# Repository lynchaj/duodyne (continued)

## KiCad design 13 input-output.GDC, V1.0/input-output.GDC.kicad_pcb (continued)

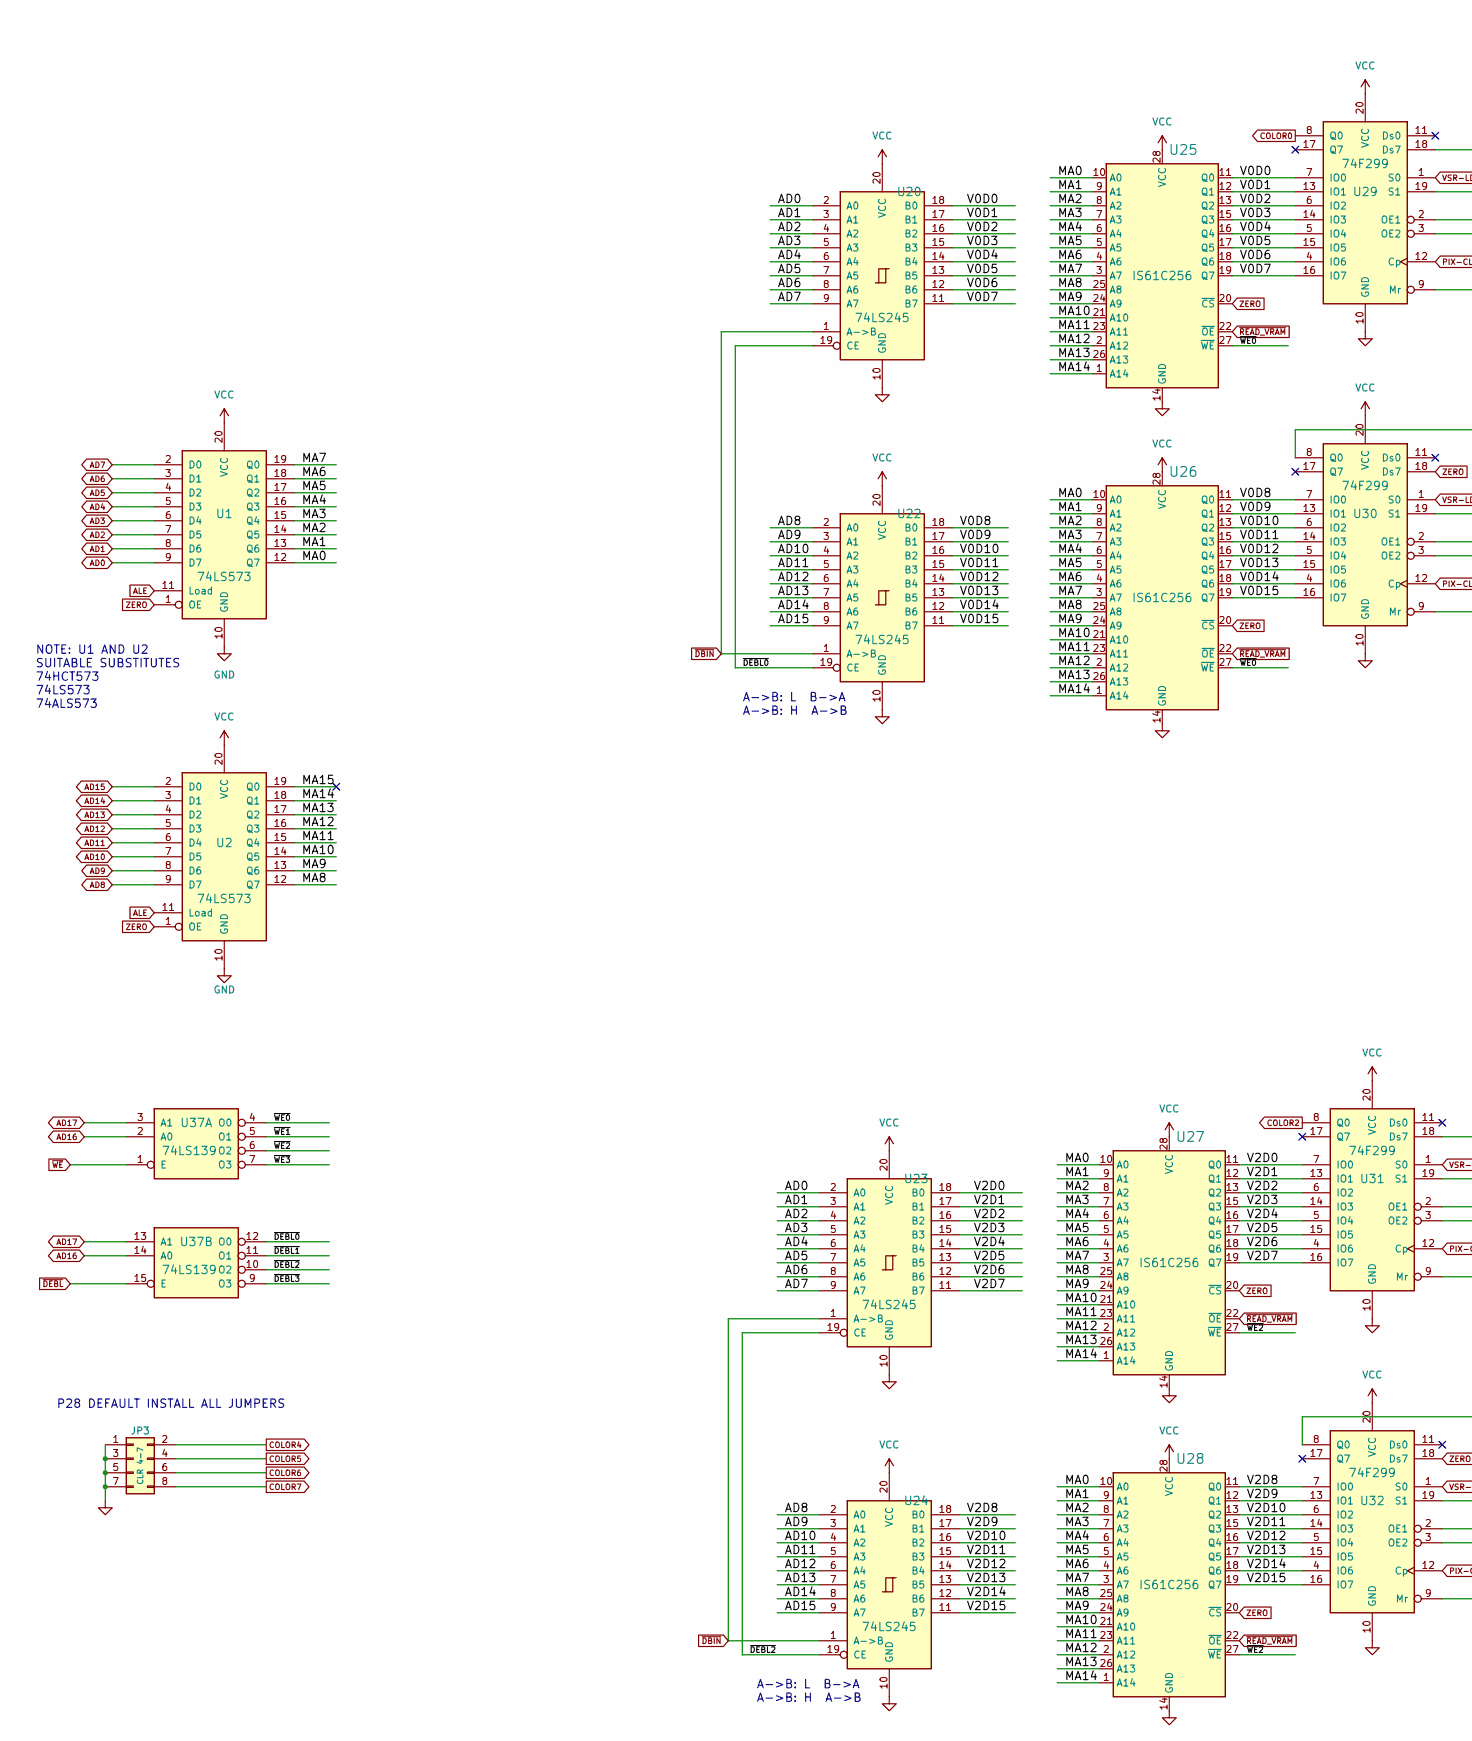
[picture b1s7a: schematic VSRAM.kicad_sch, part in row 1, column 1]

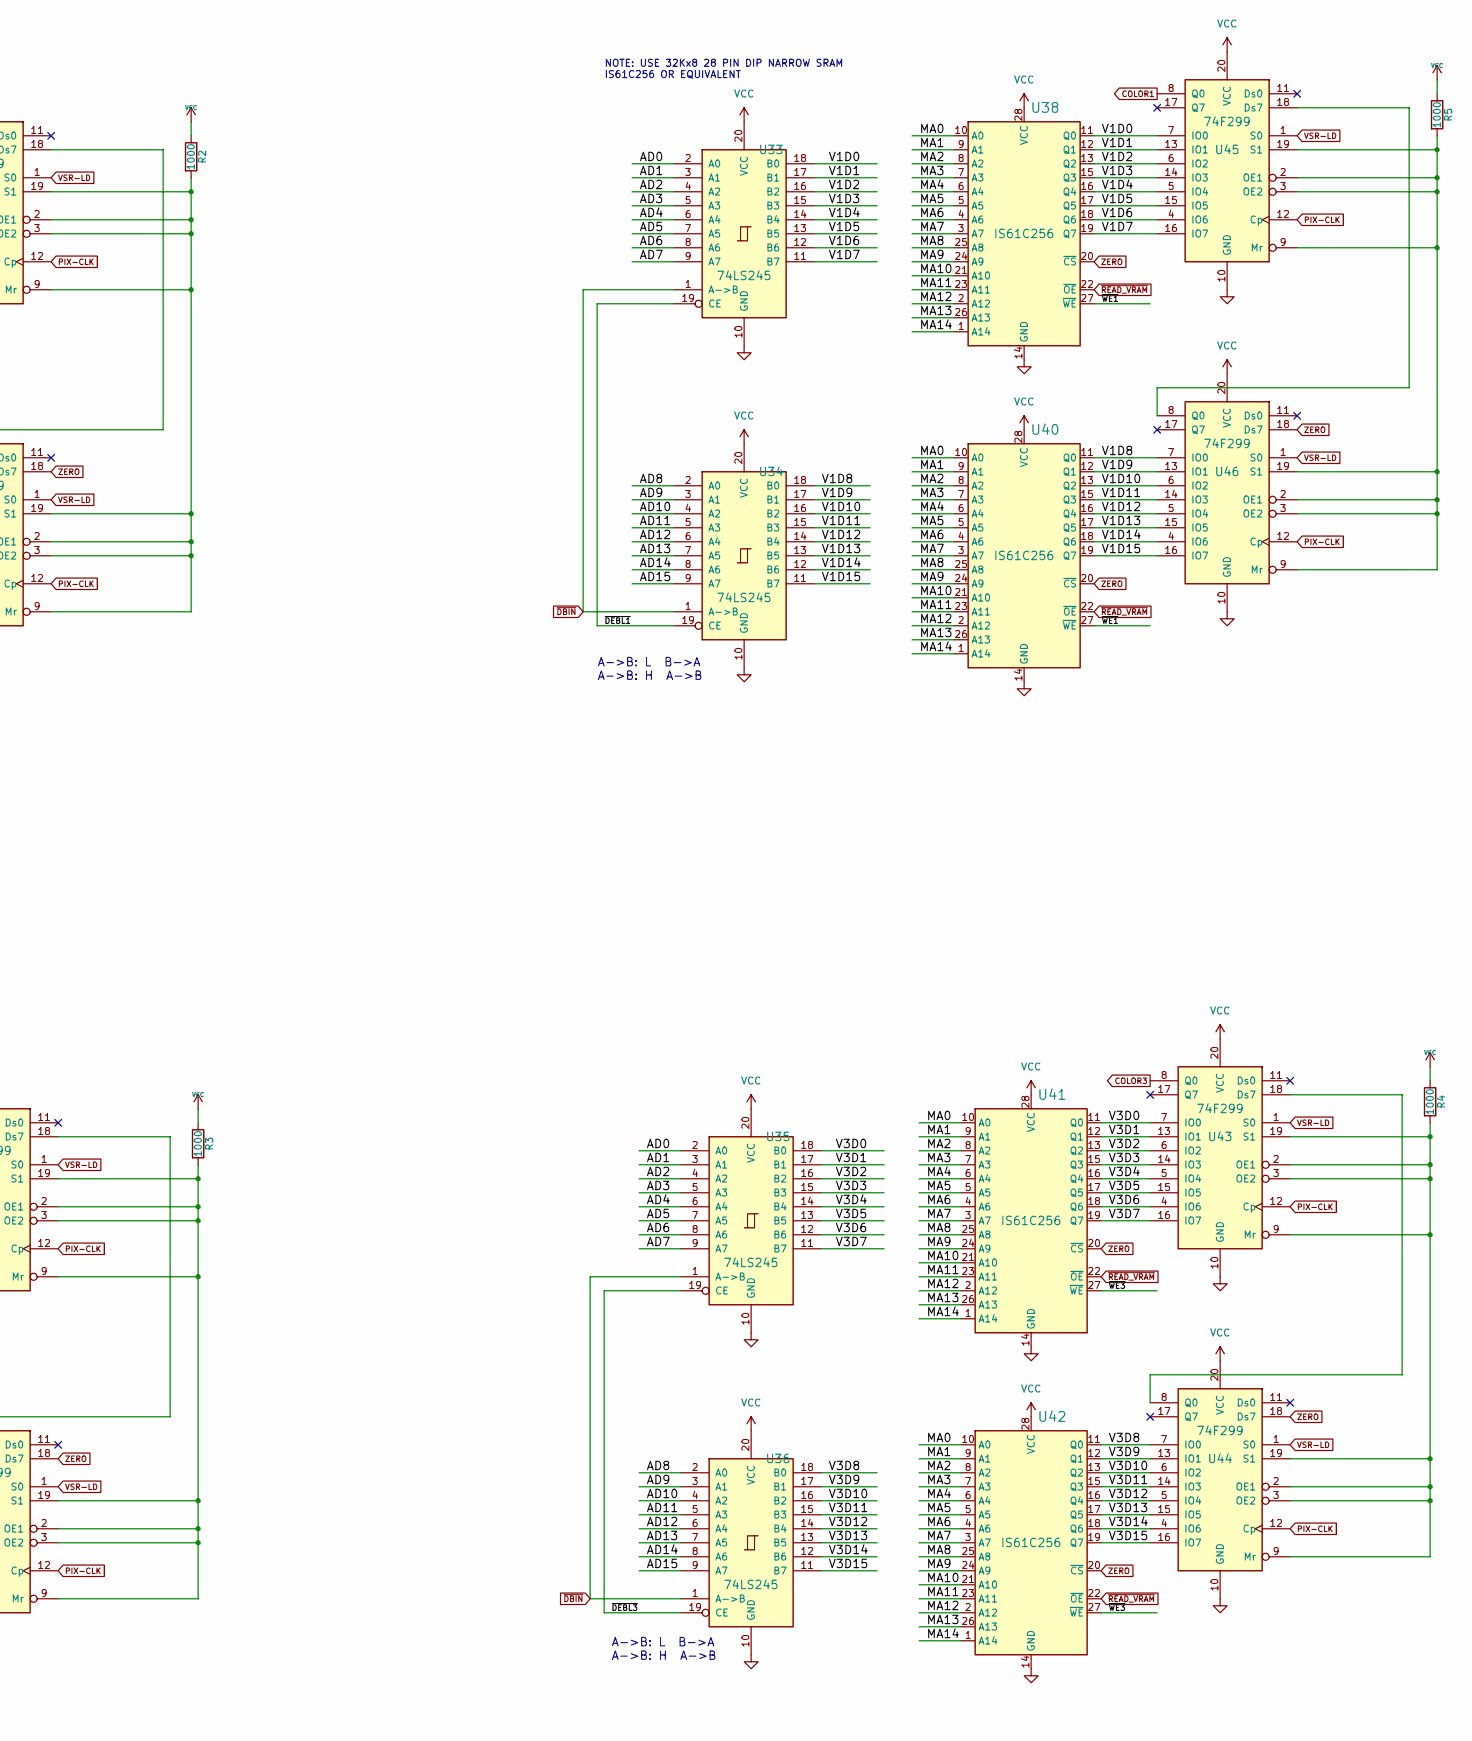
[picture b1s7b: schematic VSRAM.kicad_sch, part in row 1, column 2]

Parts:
JP3: CLR 4-7; PinHeader_2x04_P2.54mm_Vertical
R2, R3, R4, R5: 1000; R_Axial_DIN0207_L6.3mm_D2.5mm_P7.62mm_Horizontal
U1, U2: 74LS573; DIP-20_W7.62mm_Socket
U20, U22, U23, U24, U33, U34, U35, U36: 74LS245; DIP-20_W7.62mm_Socket
U25, U26, U27, U28, U38, U40, U41, U42: IS61C256; DIP-28_W7.62mm_Socket
U29, U30, U31, U32, U43, U44, U45, U46: 74F299; DIP-20_W7.62mm_Socket
U37: 74LS139; DIP-16_W7.62mm_Socket

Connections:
/VSRAM/MA0: U1.12 (Q7), U25.10 (A0), U26.10 (A0), U27.10 (A0), U28.10 (A0), U38.10 (A0), U40.10 (A0), U41.10 (A0), U42.10 (A0)
/VSRAM/MA1: U1.13 (Q6), U25.9 (A1), U26.9 (A1), U27.9 (A1), U28.9 (A1), U38.9 (A1), U40.9 (A1), U41.9 (A1), U42.9 (A1)
/VSRAM/MA2: U1.14 (Q5), U25.8 (A2), U26.8 (A2), U27.8 (A2), U28.8 (A2), U38.8 (A2), U40.8 (A2), U41.8 (A2), U42.8 (A2)
/VSRAM/MA3: U1.15 (Q4), U25.7 (A3), U26.7 (A3), U27.7 (A3), U28.7 (A3), U38.7 (A3), U40.7 (A3), U41.7 (A3), U42.7 (A3)
/VSRAM/MA4: U1.16 (Q3), U25.6 (A4), U26.6 (A4), U27.6 (A4), U28.6 (A4), U38.6 (A4), U40.6 (A4), U41.6 (A4), U42.6 (A4)
/VSRAM/MA5: U1.17 (Q2), U25.5 (A5), U26.5 (A5), U27.5 (A5), U28.5 (A5), U38.5 (A5), U40.5 (A5), U41.5 (A5), U42.5 (A5)
/VSRAM/MA6: U1.18 (Q1), U25.4 (A6), U26.4 (A6), U27.4 (A6), U28.4 (A6), U38.4 (A6), U40.4 (A6), U41.4 (A6), U42.4 (A6)
/VSRAM/MA7: U1.19 (Q0), U25.3 (A7), U26.3 (A7), U27.3 (A7), U28.3 (A7), U38.3 (A7), U40.3 (A7), U41.3 (A7), U42.3 (A7)
/VSRAM/MA8: U2.12 (Q7), U25.25 (A8), U26.25 (A8), U27.25 (A8), U28.25 (A8), U38.25 (A8), U40.25 (A8), U41.25 (A8), U42.25 (A8)
/VSRAM/MA9: U2.13 (Q6), U25.24 (A9), U26.24 (A9), U27.24 (A9), U28.24 (A9), U38.24 (A9), U40.24 (A9), U41.24 (A9), U42.24 (A9)
/VSRAM/MA10: U2.14 (Q5), U25.21 (A10), U26.21 (A10), U27.21 (A10), U28.21 (A10), U38.21 (A10), U40.21 (A10), U41.21 (A10), U42.21 (A10)
/VSRAM/MA11: U2.15 (Q4), U25.23 (A11), U26.23 (A11), U27.23 (A11), U28.23 (A11), U38.23 (A11), U40.23 (A11), U41.23 (A11), U42.23 (A11)
/VSRAM/MA12: U2.16 (Q3), U25.2 (A12), U26.2 (A12), U27.2 (A12), U28.2 (A12), U38.2 (A12), U40.2 (A12), U41.2 (A12), U42.2 (A12)
/VSRAM/MA13: U2.17 (Q2), U25.26 (A13), U26.26 (A13), U27.26 (A13), U28.26 (A13), U38.26 (A13), U40.26 (A13), U41.26 (A13), U42.26 (A13)
/VSRAM/MA14: U2.18 (Q1), U25.1 (A14), U26.1 (A14), U27.1 (A14), U28.1 (A14), U38.1 (A14), U40.1 (A14), U41.1 (A14), U42.1 (A14)
/VSRAM/MA15: U2.19 (Q0)
/VSRAM/V0D0: U20.18 (B0), U25.11 (Q0), U29.7 (IO0)
/VSRAM/V0D1: U20.17 (B1), U25.12 (Q1), U29.13 (IO1)
/VSRAM/V0D2: U20.16 (B2), U25.13 (Q2), U29.6 (IO2)
/VSRAM/V0D3: U20.15 (B3), U25.15 (Q3), U29.14 (IO3)
/VSRAM/V0D4: U20.14 (B4), U25.16 (Q4), U29.5 (IO4)
/VSRAM/V0D5: U20.13 (B5), U25.17 (Q5), U29.15 (IO5)
/VSRAM/V0D6: U20.12 (B6), U25.18 (Q6), U29.4 (IO6)
/VSRAM/V0D7: U20.11 (B7), U25.19 (Q7), U29.16 (IO7)
/VSRAM/V0D8: U22.18 (B0), U26.11 (Q0), U30.7 (IO0)
/VSRAM/V0D9: U22.17 (B1), U26.12 (Q1), U30.13 (IO1)
/VSRAM/V0D10: U22.16 (B2), U26.13 (Q2), U30.6 (IO2)
/VSRAM/V0D11: U22.15 (B3), U26.15 (Q3), U30.14 (IO3)
/VSRAM/V0D12: U22.14 (B4), U26.16 (Q4), U30.5 (IO4)
/VSRAM/V0D13: U22.13 (B5), U26.17 (Q5), U30.15 (IO5)
/VSRAM/V0D14: U22.12 (B6), U26.18 (Q6), U30.4 (IO6)
/VSRAM/V0D15: U22.11 (B7), U26.19 (Q7), U30.16 (IO7)
/VSRAM/V1D0: U33.18 (B0), U38.11 (Q0), U45.7 (IO0)
/VSRAM/V1D1: U33.17 (B1), U38.12 (Q1), U45.13 (IO1)
/VSRAM/V1D2: U33.16 (B2), U38.13 (Q2), U45.6 (IO2)
/VSRAM/V1D3: U33.15 (B3), U38.15 (Q3), U45.14 (IO3)
/VSRAM/V1D4: U33.14 (B4), U38.16 (Q4), U45.5 (IO4)
/VSRAM/V1D5: U33.13 (B5), U38.17 (Q5), U45.15 (IO5)
/VSRAM/V1D6: U33.12 (B6), U38.18 (Q6), U45.4 (IO6)
/VSRAM/V1D7: U33.11 (B7), U38.19 (Q7), U45.16 (IO7)
/VSRAM/V1D8: U34.18 (B0), U40.11 (Q0), U46.7 (IO0)
/VSRAM/V1D9: U34.17 (B1), U40.12 (Q1), U46.13 (IO1)
/VSRAM/V1D10: U34.16 (B2), U40.13 (Q2), U46.6 (IO2)
/VSRAM/V1D11: U34.15 (B3), U40.15 (Q3), U46.14 (IO3)
/VSRAM/V1D12: U34.14 (B4), U40.16 (Q4), U46.5 (IO4)
/VSRAM/V1D13: U34.13 (B5), U40.17 (Q5), U46.15 (IO5)
/VSRAM/V1D14: U34.12 (B6), U40.18 (Q6), U46.4 (IO6)
/VSRAM/V1D15: U34.11 (B7), U40.19 (Q7), U46.16 (IO7)
/VSRAM/V2D0: U23.18 (B0), U27.11 (Q0), U31.7 (IO0)
/VSRAM/V2D1: U23.17 (B1), U27.12 (Q1), U31.13 (IO1)
/VSRAM/V2D2: U23.16 (B2), U27.13 (Q2), U31.6 (IO2)
/VSRAM/V2D3: U23.15 (B3), U27.15 (Q3), U31.14 (IO3)
/VSRAM/V2D4: U23.14 (B4), U27.16 (Q4), U31.5 (IO4)
/VSRAM/V2D5: U23.13 (B5), U27.17 (Q5), U31.15 (IO5)
/VSRAM/V2D6: U23.12 (B6), U27.18 (Q6), U31.4 (IO6)
/VSRAM/V2D7: U23.11 (B7), U27.19 (Q7), U31.16 (IO7)
/VSRAM/V2D8: U24.18 (B0), U28.11 (Q0), U32.7 (IO0)
/VSRAM/V2D9: U24.17 (B1), U28.12 (Q1), U32.13 (IO1)
/VSRAM/V2D10: U24.16 (B2), U28.13 (Q2), U32.6 (IO2)
/VSRAM/V2D11: U24.15 (B3), U28.15 (Q3), U32.14 (IO3)
/VSRAM/V2D12: U24.14 (B4), U28.16 (Q4), U32.5 (IO4)
/VSRAM/V2D13: U24.13 (B5), U28.17 (Q5), U32.15 (IO5)
/VSRAM/V2D14: U24.12 (B6), U28.18 (Q6), U32.4 (IO6)
/VSRAM/V2D15: U24.11 (B7), U28.19 (Q7), U32.16 (IO7)
/VSRAM/V3D0: U35.18 (B0), U41.11 (Q0), U43.7 (IO0)
/VSRAM/V3D1: U35.17 (B1), U41.12 (Q1), U43.13 (IO1)
/VSRAM/V3D2: U35.16 (B2), U41.13 (Q2), U43.6 (IO2)
/VSRAM/V3D3: U35.15 (B3), U41.15 (Q3), U43.14 (IO3)
/VSRAM/V3D4: U35.14 (B4), U41.16 (Q4), U43.5 (IO4)
/VSRAM/V3D5: U35.13 (B5), U41.17 (Q5), U43.15 (IO5)
/VSRAM/V3D6: U35.12 (B6), U41.18 (Q6), U43.4 (IO6)
/VSRAM/V3D7: U35.11 (B7), U41.19 (Q7), U43.16 (IO7)
/VSRAM/V3D8: U36.18 (B0), U42.11 (Q0), U44.7 (IO0)
/VSRAM/V3D9: U36.17 (B1), U42.12 (Q1), U44.13 (IO1)
/VSRAM/V3D10: U36.16 (B2), U42.13 (Q2), U44.6 (IO2)
/VSRAM/V3D11: U36.15 (B3), U42.15 (Q3), U44.14 (IO3)
/VSRAM/V3D12: U36.14 (B4), U42.16 (Q4), U44.5 (IO4)
/VSRAM/V3D13: U36.13 (B5), U42.17 (Q5), U44.15 (IO5)
/VSRAM/V3D14: U36.12 (B6), U42.18 (Q6), U44.4 (IO6)
/VSRAM/V3D15: U36.11 (B7), U42.19 (Q7), U44.16 (IO7)
/VSRAM/~DEBL0: U20.19 (CE), U22.19 (CE), U37.12 (O0)
/VSRAM/~DEBL1: U33.19 (CE), U34.19 (CE), U37.11 (O1)
/VSRAM/~DEBL2: U23.19 (CE), U24.19 (CE), U37.10 (O2)
/VSRAM/~DEBL3: U35.19 (CE), U36.19 (CE), U37.9 (O3)
/VSRAM/~WE0: U25.27 (~WE), U26.27 (~WE), U37.4 (O0)
/VSRAM/~WE1: U37.5 (O1), U38.27 (~WE), U40.27 (~WE)
/VSRAM/~WE2: U27.27 (~WE), U28.27 (~WE), U37.6 (O2)
/VSRAM/~WE3: U37.7 (O3), U41.27 (~WE), U42.27 (~WE)
AD0: U1.9 (D7), U20.2 (A0), U23.2 (A0), U33.2 (A0), U35.2 (A0); also elsewhere on the board
AD1: U1.8 (D6), U20.3 (A1), U23.3 (A1), U33.3 (A1), U35.3 (A1); also elsewhere on the board
AD2: U1.7 (D5), U20.4 (A2), U23.4 (A2), U33.4 (A2), U35.4 (A2); also elsewhere on the board
AD3: U1.6 (D4), U20.5 (A3), U23.5 (A3), U33.5 (A3), U35.5 (A3); also elsewhere on the board
AD4: U1.5 (D3), U20.6 (A4), U23.6 (A4), U33.6 (A4), U35.6 (A4); also elsewhere on the board
AD5: U1.4 (D2), U20.7 (A5), U23.7 (A5), U33.7 (A5), U35.7 (A5); also elsewhere on the board
AD6: U1.3 (D1), U20.8 (A6), U23.8 (A6), U33.8 (A6), U35.8 (A6); also elsewhere on the board
AD7: U1.2 (D0), U20.9 (A7), U23.9 (A7), U33.9 (A7), U35.9 (A7); also elsewhere on the board
AD8: U2.9 (D7), U22.2 (A0), U24.2 (A0), U34.2 (A0), U36.2 (A0); also elsewhere on the board
AD9: U2.8 (D6), U22.3 (A1), U24.3 (A1), U34.3 (A1), U36.3 (A1); also elsewhere on the board
AD10: U2.7 (D5), U22.4 (A2), U24.4 (A2), U34.4 (A2), U36.4 (A2); also elsewhere on the board
AD11: U2.6 (D4), U22.5 (A3), U24.5 (A3), U34.5 (A3), U36.5 (A3); also elsewhere on the board
AD12: U2.5 (D3), U22.6 (A4), U24.6 (A4), U34.6 (A4), U36.6 (A4); also elsewhere on the board
AD13: U2.4 (D2), U22.7 (A5), U24.7 (A5), U34.7 (A5), U36.7 (A5); also elsewhere on the board
AD14: U2.3 (D1), U22.8 (A6), U24.8 (A6), U34.8 (A6), U36.8 (A6); also elsewhere on the board
AD15: U2.2 (D0), U22.9 (A7), U24.9 (A7), U34.9 (A7), U36.9 (A7); also elsewhere on the board
AD16: U37.2 (A0), U37.14 (A0); also elsewhere on the board
AD17: U37.3 (A1), U37.13 (A1); also elsewhere on the board
ALE: U1.11 (Load), U2.11 (Load); also elsewhere on the board
COLOR0: U29.8 (Q0); also elsewhere on the board
COLOR1: U45.8 (Q0); also elsewhere on the board
COLOR2: U31.8 (Q0); also elsewhere on the board
COLOR3: U43.8 (Q0); also elsewhere on the board
COLOR4: JP3.2; also elsewhere on the board
COLOR5: JP3.4; also elsewhere on the board
COLOR6: JP3.6; also elsewhere on the board
COLOR7: JP3.8; also elsewhere on the board
unnamed: R2.2, U29.2 (OE1), U29.3 (OE2), U29.9 (Mr), U29.19 (S1), U30.2 (OE1), U30.3 (OE2), U30.9 (Mr), U30.19 (S1)
unnamed: R3.2, U31.2 (OE1), U31.3 (OE2), U31.9 (Mr), U31.19 (S1), U32.2 (OE1), U32.3 (OE2), U32.9 (Mr), U32.19 (S1)
unnamed: R4.2, U43.2 (OE1), U43.3 (OE2), U43.9 (Mr), U43.19 (S1), U44.2 (OE1), U44.3 (OE2), U44.9 (Mr), U44.19 (S1)
unnamed: R5.2, U45.2 (OE1), U45.3 (OE2), U45.9 (Mr), U45.19 (S1), U46.2 (OE1), U46.3 (OE2), U46.9 (Mr), U46.19 (S1)
unnamed: U29.18 (Ds7), U30.8 (Q0)
unnamed: U31.18 (Ds7), U32.8 (Q0)
unnamed: U43.18 (Ds7), U44.8 (Q0)
unnamed: U45.18 (Ds7), U46.8 (Q0)
PIX-CLK: U29.12 (Cp), U30.12 (Cp), U31.12 (Cp), U32.12 (Cp), U43.12 (Cp), U44.12 (Cp), U45.12 (Cp), U46.12 (Cp); also elsewhere on the board
VCC: R2.1, R3.1, R4.1, R5.1, U1.20 (VCC), U2.20 (VCC), U20.20 (VCC), U22.20 (VCC), U23.20 (VCC), U24.20 (VCC), U25.28 (VCC), U26.28 (VCC), U27.28 (VCC), U28.28 (VCC), U29.20 (VCC), U30.20 (VCC), U31.20 (VCC), U32.20 (VCC), U33.20 (VCC), U34.20 (VCC), U35.20 (VCC), U36.20 (VCC), U38.28 (VCC), U40.28 (VCC), U41.28 (VCC), U42.28 (VCC), U43.20 (VCC), U44.20 (VCC), U45.20 (VCC), U46.20 (VCC); also elsewhere on the board
VSR-LD: U29.1 (S0), U30.1 (S0), U31.1 (S0), U32.1 (S0), U43.1 (S0), U44.1 (S0), U45.1 (S0), U46.1 (S0); also elsewhere on the board
ZERO: U1.1 (OE), U2.1 (OE), U25.20 (~CS), U26.20 (~CS), U27.20 (~CS), U28.20 (~CS), U30.18 (Ds7), U32.18 (Ds7), U38.20 (~CS), U40.20 (~CS), U41.20 (~CS), U42.20 (~CS), U44.18 (Ds7), U46.18 (Ds7); also elsewhere on the board
~DBIN: U20.1 (A->B), U22.1 (A->B), U23.1 (A->B), U24.1 (A->B), U33.1 (A->B), U34.1 (A->B), U35.1 (A->B), U36.1 (A->B); also elsewhere on the board
~DEBL: U37.15 (E); also elsewhere on the board
~READ_VRAM: U25.22 (~OE), U26.22 (~OE), U27.22 (~OE), U28.22 (~OE), U38.22 (~OE), U40.22 (~OE), U41.22 (~OE), U42.22 (~OE); also elsewhere on the board
~WE: U37.1 (E); also elsewhere on the board

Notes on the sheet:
A->B: L B->A A->B: H A->B
NOTE: USE 32Kx8 28 PIN DIP NARROW SRAM IS61C256 OR EQUIVALENT
P28 DEFAULT INSTALL ALL JUMPERS
NOTE: U1 AND U2 SUITABLE SUBSTITUTES 74HCT573 74LS573 74ALS573

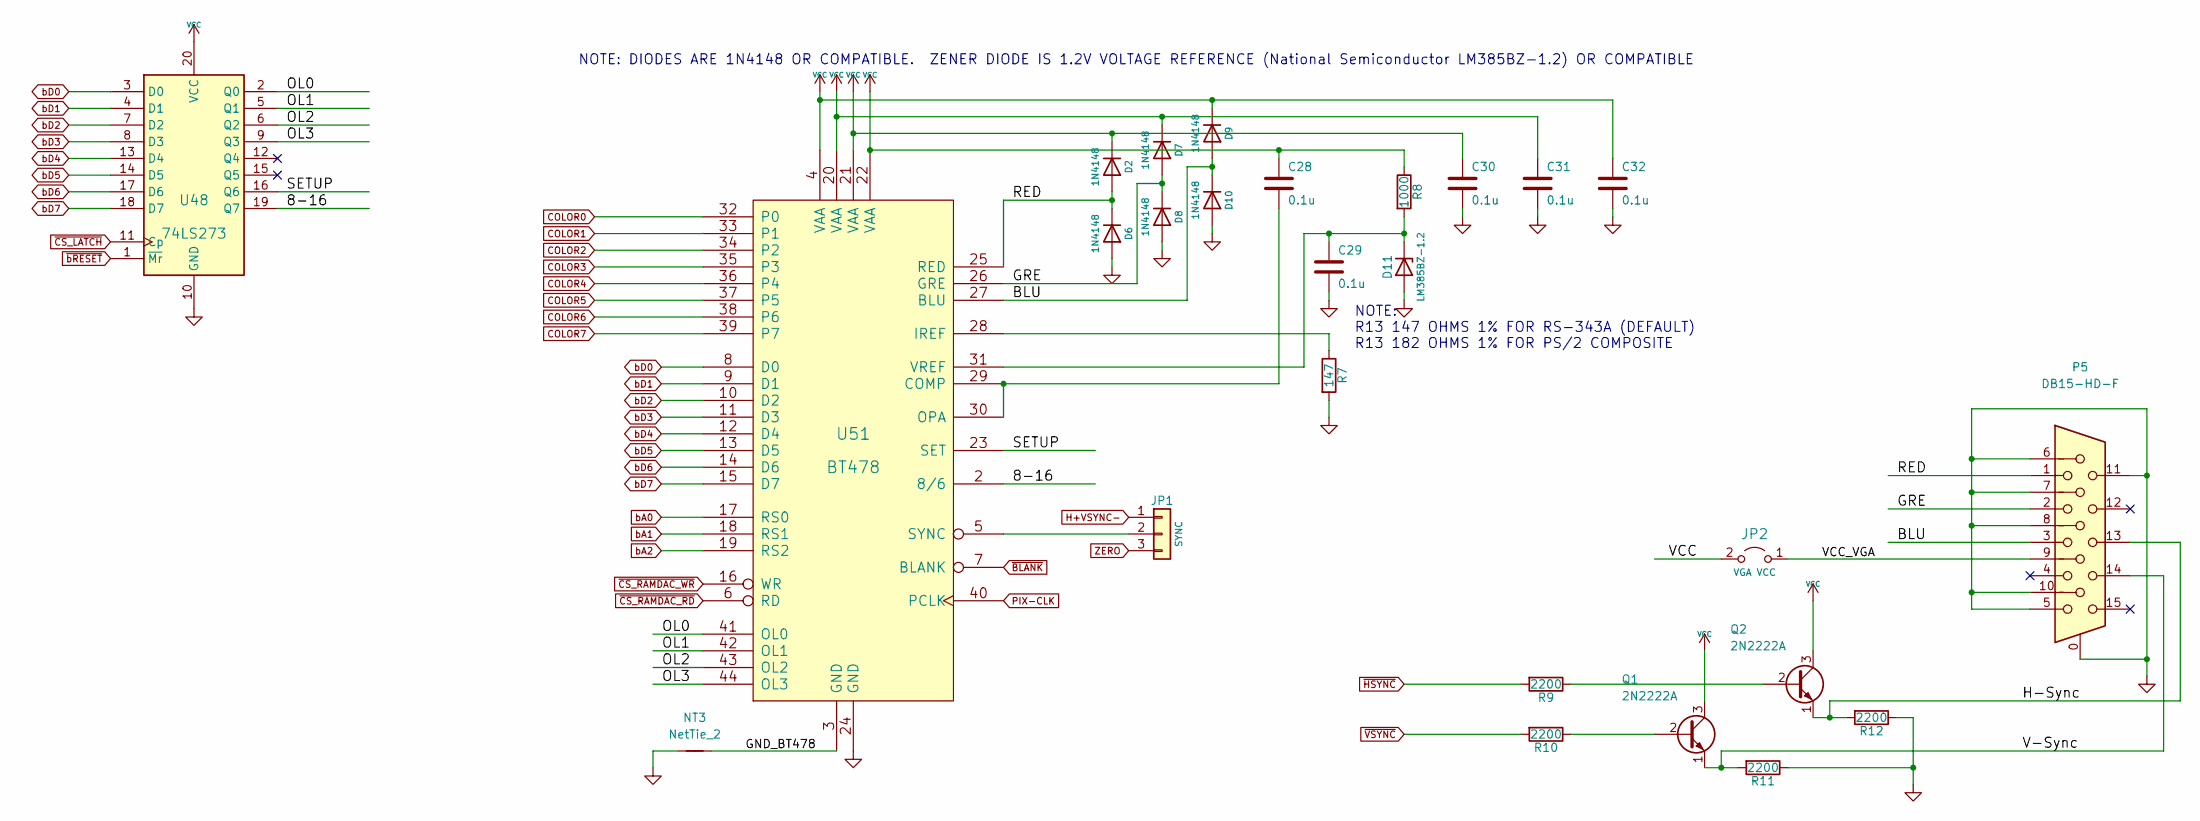
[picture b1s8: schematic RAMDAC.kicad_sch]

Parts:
C28, C29, C30, C31, C32: 0.1u; C_Disc_D5.0mm_W2.5mm_P5.00mm
D2, D6, D7, D8, D9, D10: 1N4148; D_DO-41_SOD81_P7.62mm_Horizontal
D11: LM385BZ-1.2; TO-92L_HandSolder
JP1: SYNC; PinHeader_1x03_P2.54mm_Vertical
JP2: VGA VCC; PinHeader_1x02_P2.54mm_Vertical
NT3: NetTie_2; NetTie-2_THT_Pad0.3mm
P5: DB15-HD-F; DSUB-15-HD_Female_Horizontal_P2.29x1.98mm_EdgePinOffset3.03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
Q1, Q2: 2N2222A; TO-92L_HandSolder
R7: 147; R_Axial_DIN0207_L6.3mm_D2.5mm_P7.62mm_Horizontal
R8: 1000; R_Axial_DIN0207_L6.3mm_D2.5mm_P7.62mm_Horizontal
R9, R10, R11, R12: 2200; R_Axial_DIN0207_L6.3mm_D2.5mm_P7.62mm_Horizontal
U48: 74LS273; DIP-20_W7.62mm_Socket
U51: BT478; PLCC-44_THT-Socket

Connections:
/RAMDAC/8-16: U48.19 (Q7), U51.2 (8/6)
/RAMDAC/BLU: D9.2 (A), D10.1 (K), P5.3, U51.27 (BLU)
/RAMDAC/GND_BT478: NT3.2, U51.3 (GND)
/RAMDAC/GRE: D7.2 (A), D8.1 (K), P5.2, U51.26 (GRE)
/RAMDAC/H-Sync: P5.13, Q2.1 (E), R12.2
/RAMDAC/OL0: U48.2 (Q0), U51.41 (OL0)
/RAMDAC/OL1: U48.5 (Q1), U51.42 (OL1)
/RAMDAC/OL2: U48.6 (Q2), U51.43 (OL2)
/RAMDAC/OL3: U48.9 (Q3), U51.44 (OL3)
/RAMDAC/RED: D2.2 (A), D6.1 (K), P5.1, U51.25 (RED)
/RAMDAC/SETUP: U48.16 (Q6), U51.23 (SET)
/RAMDAC/V-Sync: P5.14, Q1.1 (E), R11.2
/RAMDAC/VCC_VGA: JP2.1 (A), P5.9
COLOR0: U51.32 (P0); also elsewhere on the board
COLOR1: U51.33 (P1); also elsewhere on the board
COLOR2: U51.34 (P2); also elsewhere on the board
COLOR3: U51.35 (P3); also elsewhere on the board
COLOR4: U51.36 (P4); also elsewhere on the board
COLOR5: U51.37 (P5); also elsewhere on the board
COLOR6: U51.38 (P6); also elsewhere on the board
COLOR7: U51.39 (P7); also elsewhere on the board
H+VSYNC-: JP1.1; also elsewhere on the board
unnamed: C28.2, U51.29 (COMP), U51.30 (OPA)
unnamed: C29.1, D11.1 (K), R8.2, U51.31 (VREF)
unnamed: JP1.2, U51.5 (SYNC)
unnamed: Q1.2 (B), R10.1
unnamed: Q2.2 (B), R9.1
unnamed: R7.1, U51.28 (IREF)
PIX-CLK: U51.40 (PCLK); also elsewhere on the board
VCC: C28.1, C30.1, C31.1, C32.1, D2.1 (K), D7.1 (K), D9.1 (K), JP2.2 (B), Q1.3 (C), Q2.3 (C), R8.1, U48.20 (VCC), U51.4 (VAA), U51.20 (VAA), U51.21 (VAA), U51.22 (VAA); also elsewhere on the board
ZERO: JP1.3; also elsewhere on the board
bA0: U51.17 (RS0); also elsewhere on the board
bA1: U51.18 (RS1); also elsewhere on the board
bA2: U51.19 (RS2); also elsewhere on the board
bD0: U48.3 (D0), U51.8 (D0); also elsewhere on the board
bD1: U48.4 (D1), U51.9 (D1); also elsewhere on the board
bD2: U48.7 (D2), U51.10 (D2); also elsewhere on the board
bD3: U48.8 (D3), U51.11 (D3); also elsewhere on the board
bD4: U48.13 (D4), U51.12 (D4); also elsewhere on the board
bD5: U48.14 (D5), U51.13 (D5); also elsewhere on the board
bD6: U48.17 (D6), U51.14 (D6); also elsewhere on the board
bD7: U48.18 (D7), U51.15 (D7); also elsewhere on the board
~BLANK: U51.7 (BLANK); also elsewhere on the board
~CS_LATCH: U48.11 (Cp); also elsewhere on the board
~CS_RAMDAC_RD: U51.6 (RD); also elsewhere on the board
~CS_RAMDAC_WR: U51.16 (WR); also elsewhere on the board
~HSYNC: R9.2; also elsewhere on the board
~VSYNC: R10.2; also elsewhere on the board
~bRESET: U48.1 (~Mr); also elsewhere on the board

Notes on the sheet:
NOTE: R13 147 OHMS 1% FOR RS-343A (DEFAULT) R13 182 OHMS 1% FOR PS/2 COMPOSITE
NOTE: DIODES ARE 1N4148 OR COMPATIBLE. ZENER DIODE IS 1.2V VOLTAGE REFERENCE (National Semiconductor LM385BZ-1.2) OR COMPATIBLE

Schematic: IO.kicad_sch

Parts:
D3, D4, D5: LED; LED_D3.0mm_Horizontal_O3.81mm_Z2.0mm
R14, R15, R16: 470; R_Axial_DIN0207_L6.3mm_D2.5mm_P7.62mm_Horizontal
RN1: 10K; R_Array_SIP9
SW1: IO PORT ADDR; PinHeader_2x04_P2.54mm_Vertical
U5: 74LS07; DIP-14_W7.62mm
U21: 74LS688; DIP-20_W7.62mm

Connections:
unnamed: D3.1 (K), U5.12
unnamed: D3.2 (A), R14.1
unnamed: D4.1 (K), U5.8
unnamed: D4.2 (A), R15.1
unnamed: D5.1 (K), U5.10
unnamed: D5.2 (A), R16.1
unnamed: RN1.2 (R1), SW1.1, U21.18 (R7)
unnamed: RN1.3 (R2), SW1.3, U21.16 (R6)
unnamed: RN1.4 (R3), SW1.5, U21.14 (R5)
unnamed: RN1.5 (R4), SW1.7, U21.12 (R4)
unnamed: RN1.9 (R8), U21.3 (R0), U21.4 (P1), U21.5 (R1), U21.6 (P2), U21.7 (R2), U21.8 (P3), U21.9 (R3)
VCC: R14.2, R15.2, R16.2, RN1.1 (common), U21.20 (VCC); also elsewhere on the board
ZERO: SW1.2, SW1.4, SW1.6, SW1.8; also elsewhere on the board
bA4: U21.11 (P4); also elsewhere on the board
bA5: U21.13 (P5); also elsewhere on the board
bA6: U21.15 (P6); also elsewhere on the board
bA7: U21.17 (P7); also elsewhere on the board
~CS_BRD: U21.19 (P=R); also elsewhere on the board
~CS_GDC: U5.9; also elsewhere on the board
~CS_LATCH: U5.11; also elsewhere on the board
~CS_RAMDAC: U5.13; also elsewhere on the board
~bIORQ: U21.1 (G); also elsewhere on the board
~bM1: U21.2 (P0); also elsewhere on the board

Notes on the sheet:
SET IO PORT
Note: IO Address Port $C0-$CF 1-2 =off - A7 (high) 3-4 =off - A6 (high) 5-6 =on - A5 (low) 7-8 =on - A4 (low)
IO SELECTION CIRCUIT
Note: Inhibit Board Operation During Interrupts ~{M1} = low, ~{IORQ} = low

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
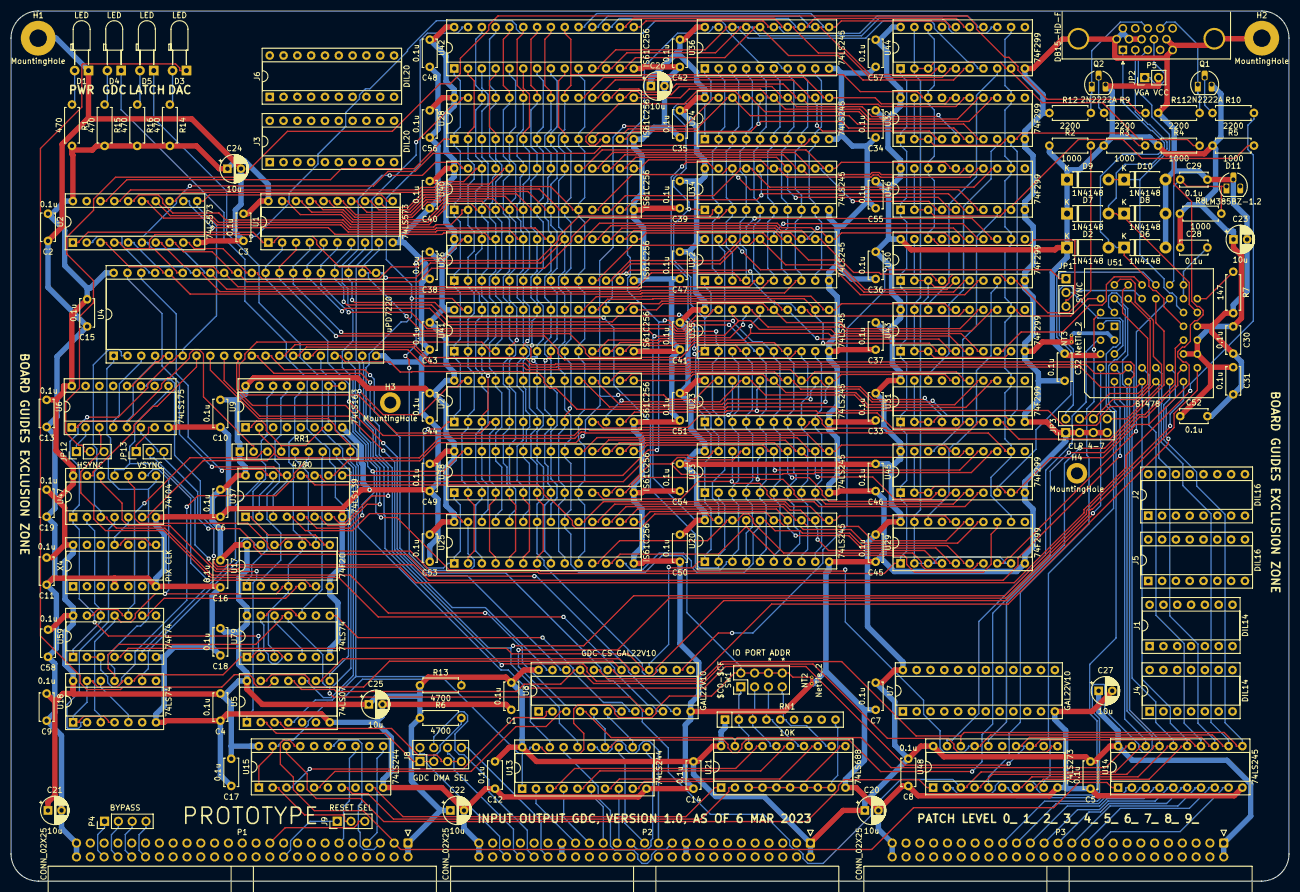
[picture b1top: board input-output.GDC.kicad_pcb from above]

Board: 2 copper layers, 235.0 x 160.0 mm, 159 parts (0 on the bottom side), 260 nets.

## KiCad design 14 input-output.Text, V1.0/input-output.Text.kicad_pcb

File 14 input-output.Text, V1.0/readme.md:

This board provides a text-only VGA monitor compatible video capability.  The intent for this prototype is to prove functionality and eventually be integrated into the GDC IO board as its text mode only subsystem.  Possibly as a mezzanine board attachment or if space allows integrated on to the GDC IO planar.

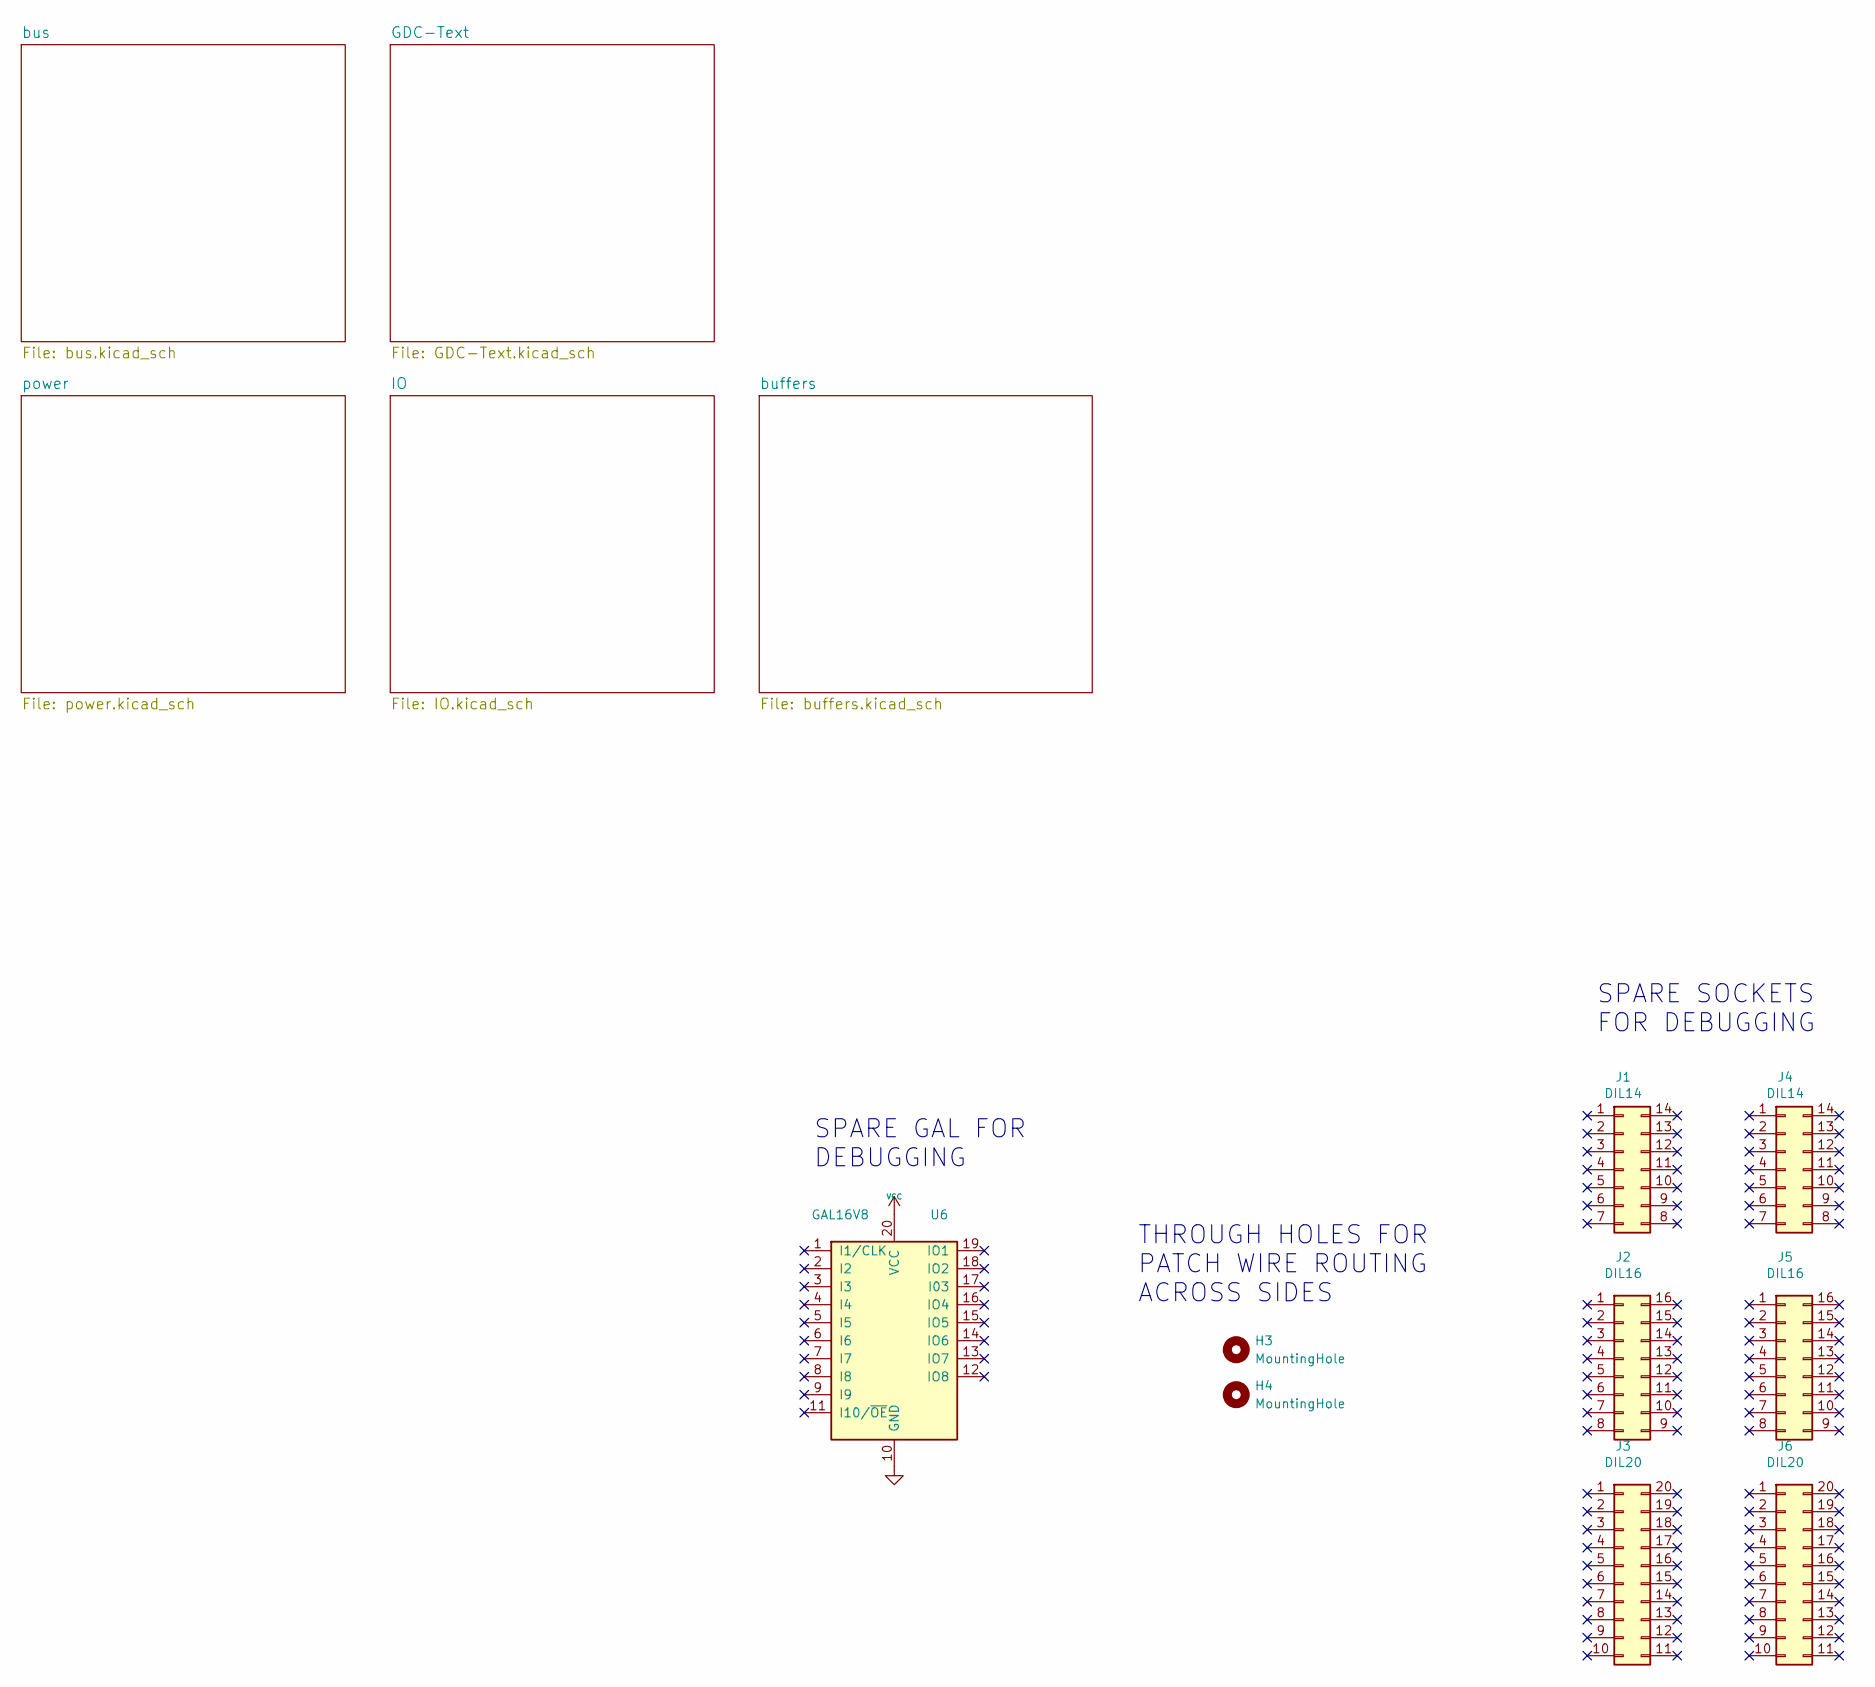
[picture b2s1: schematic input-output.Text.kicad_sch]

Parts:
H3, H4: MountingHole; MountingHole_2.2mm_M2_DIN965_Pad
J1, J4: DIL14; DIP-14_W7.62mm
J2, J5: DIL16; DIP-16_W7.62mm
J3, J6: DIL20; DIP-20_W7.62mm
U6: GAL16V8; DIP-20_W7.62mm

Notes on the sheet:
SPARE SOCKETS FOR DEBUGGING
SPARE GAL FOR DEBUGGING
THROUGH HOLES FOR PATCH WIRE ROUTING ACROSS SIDES
